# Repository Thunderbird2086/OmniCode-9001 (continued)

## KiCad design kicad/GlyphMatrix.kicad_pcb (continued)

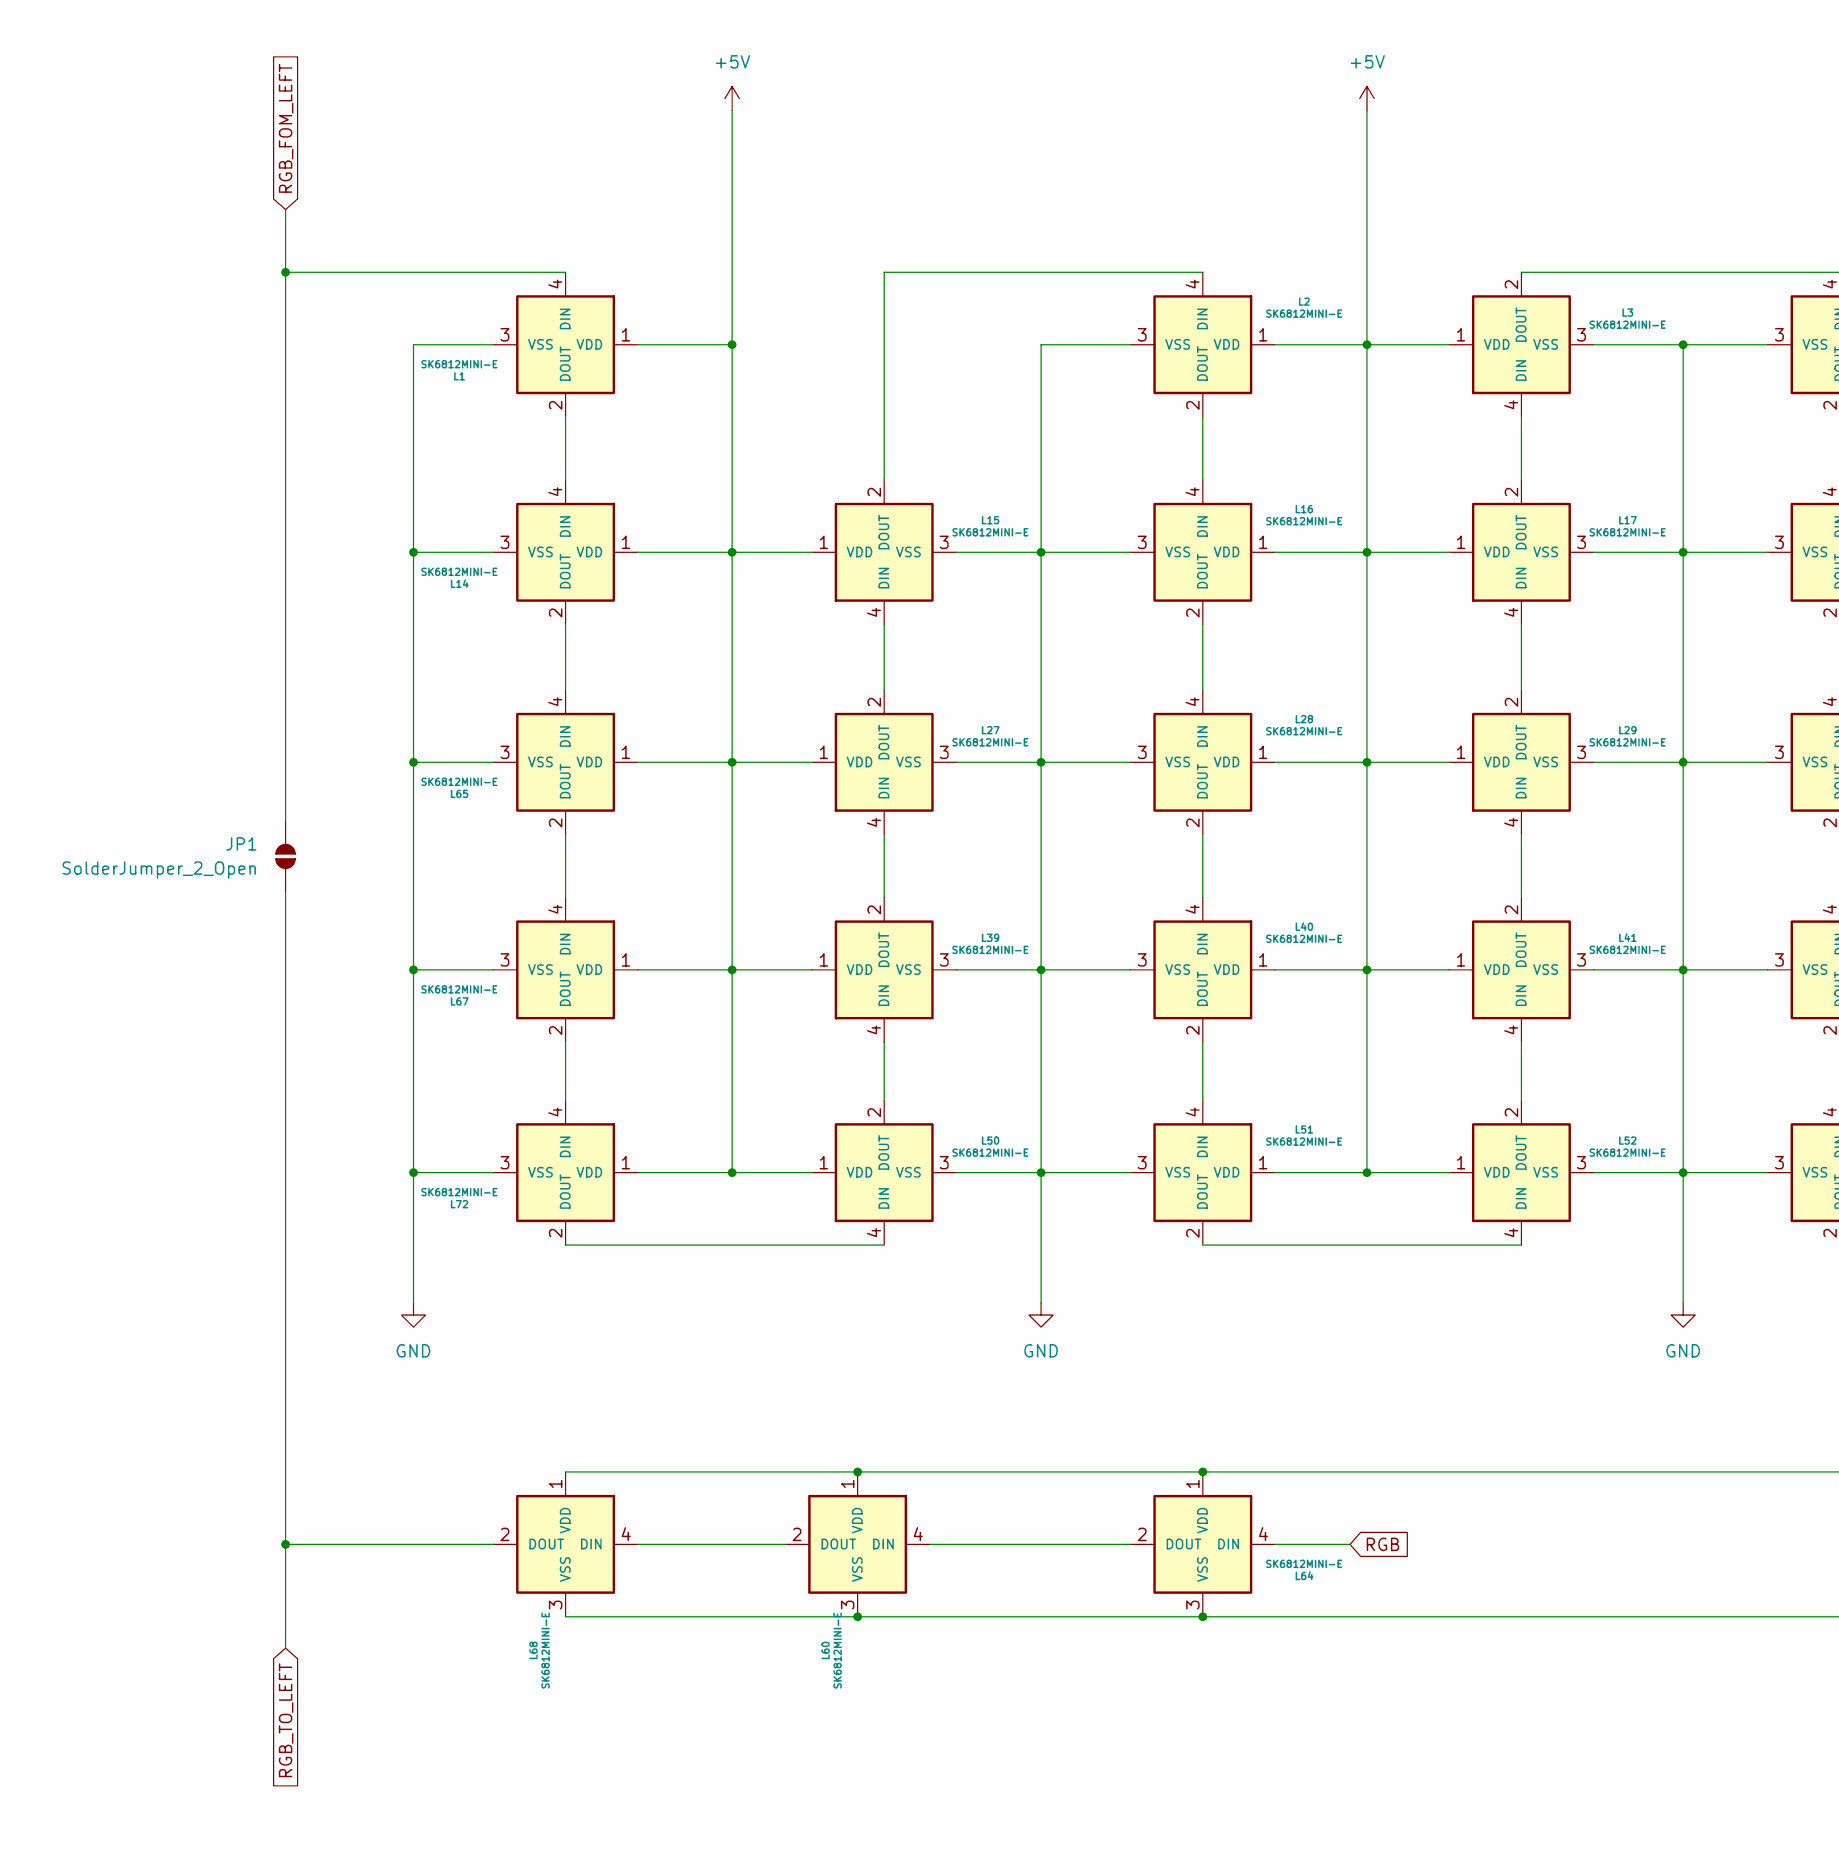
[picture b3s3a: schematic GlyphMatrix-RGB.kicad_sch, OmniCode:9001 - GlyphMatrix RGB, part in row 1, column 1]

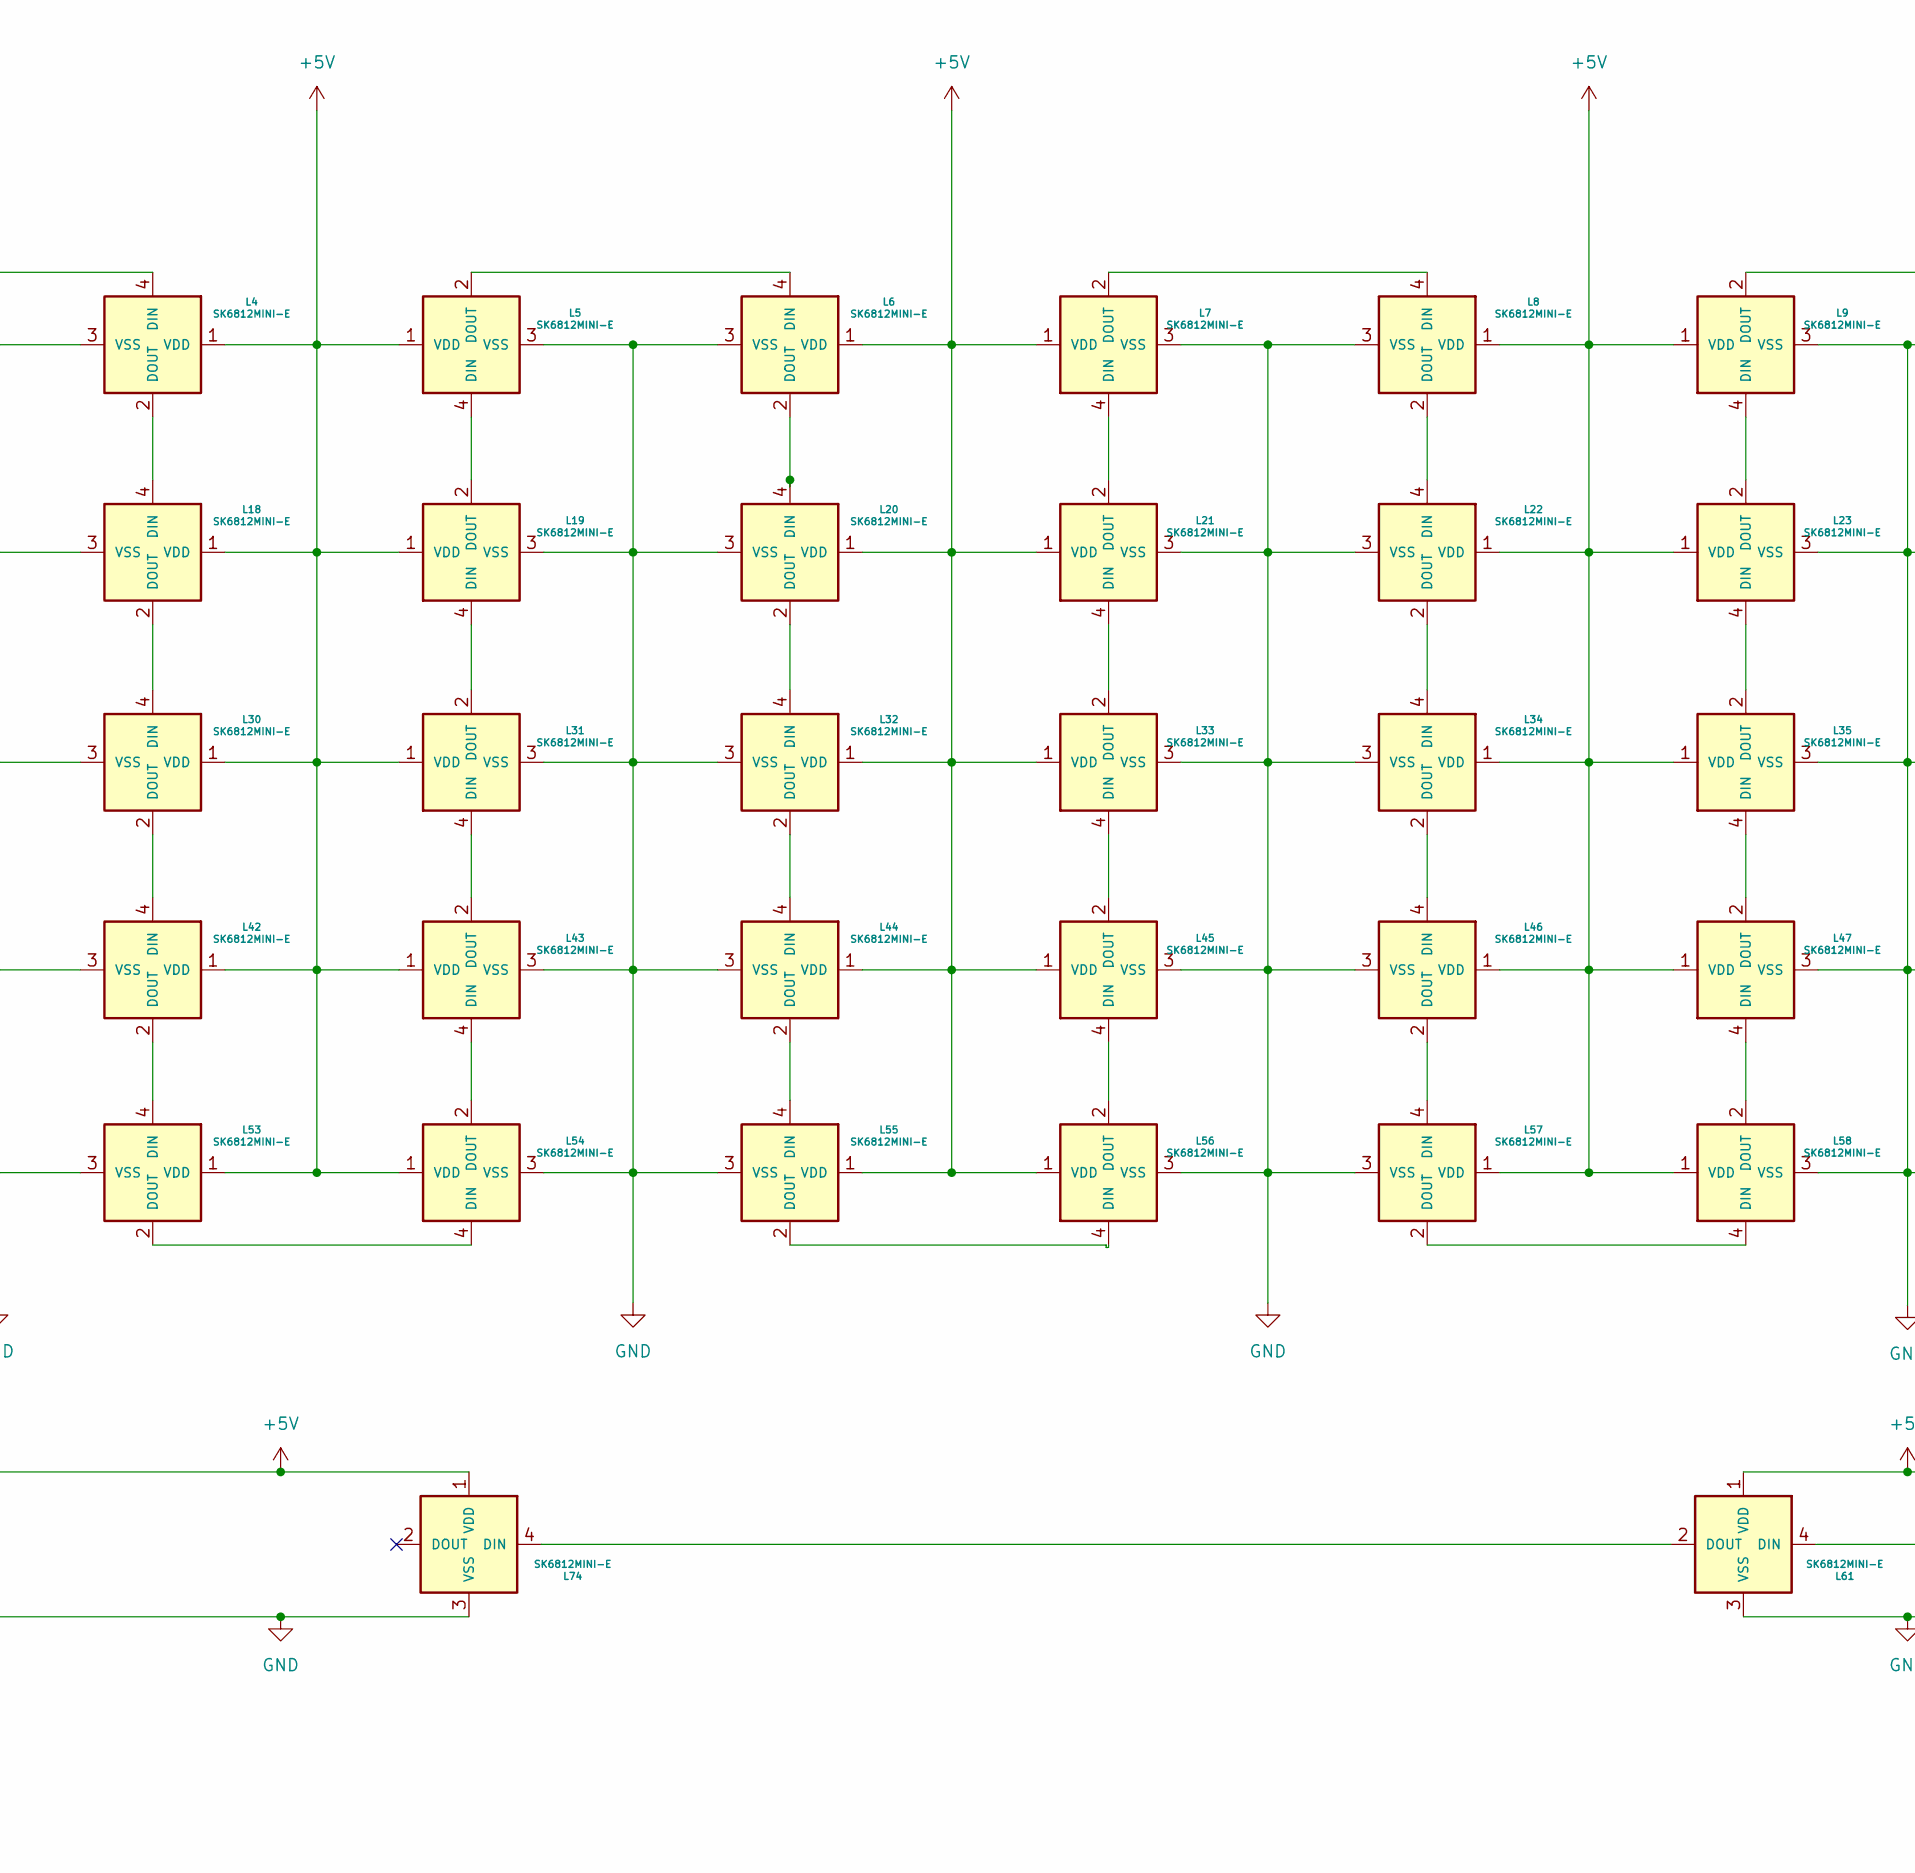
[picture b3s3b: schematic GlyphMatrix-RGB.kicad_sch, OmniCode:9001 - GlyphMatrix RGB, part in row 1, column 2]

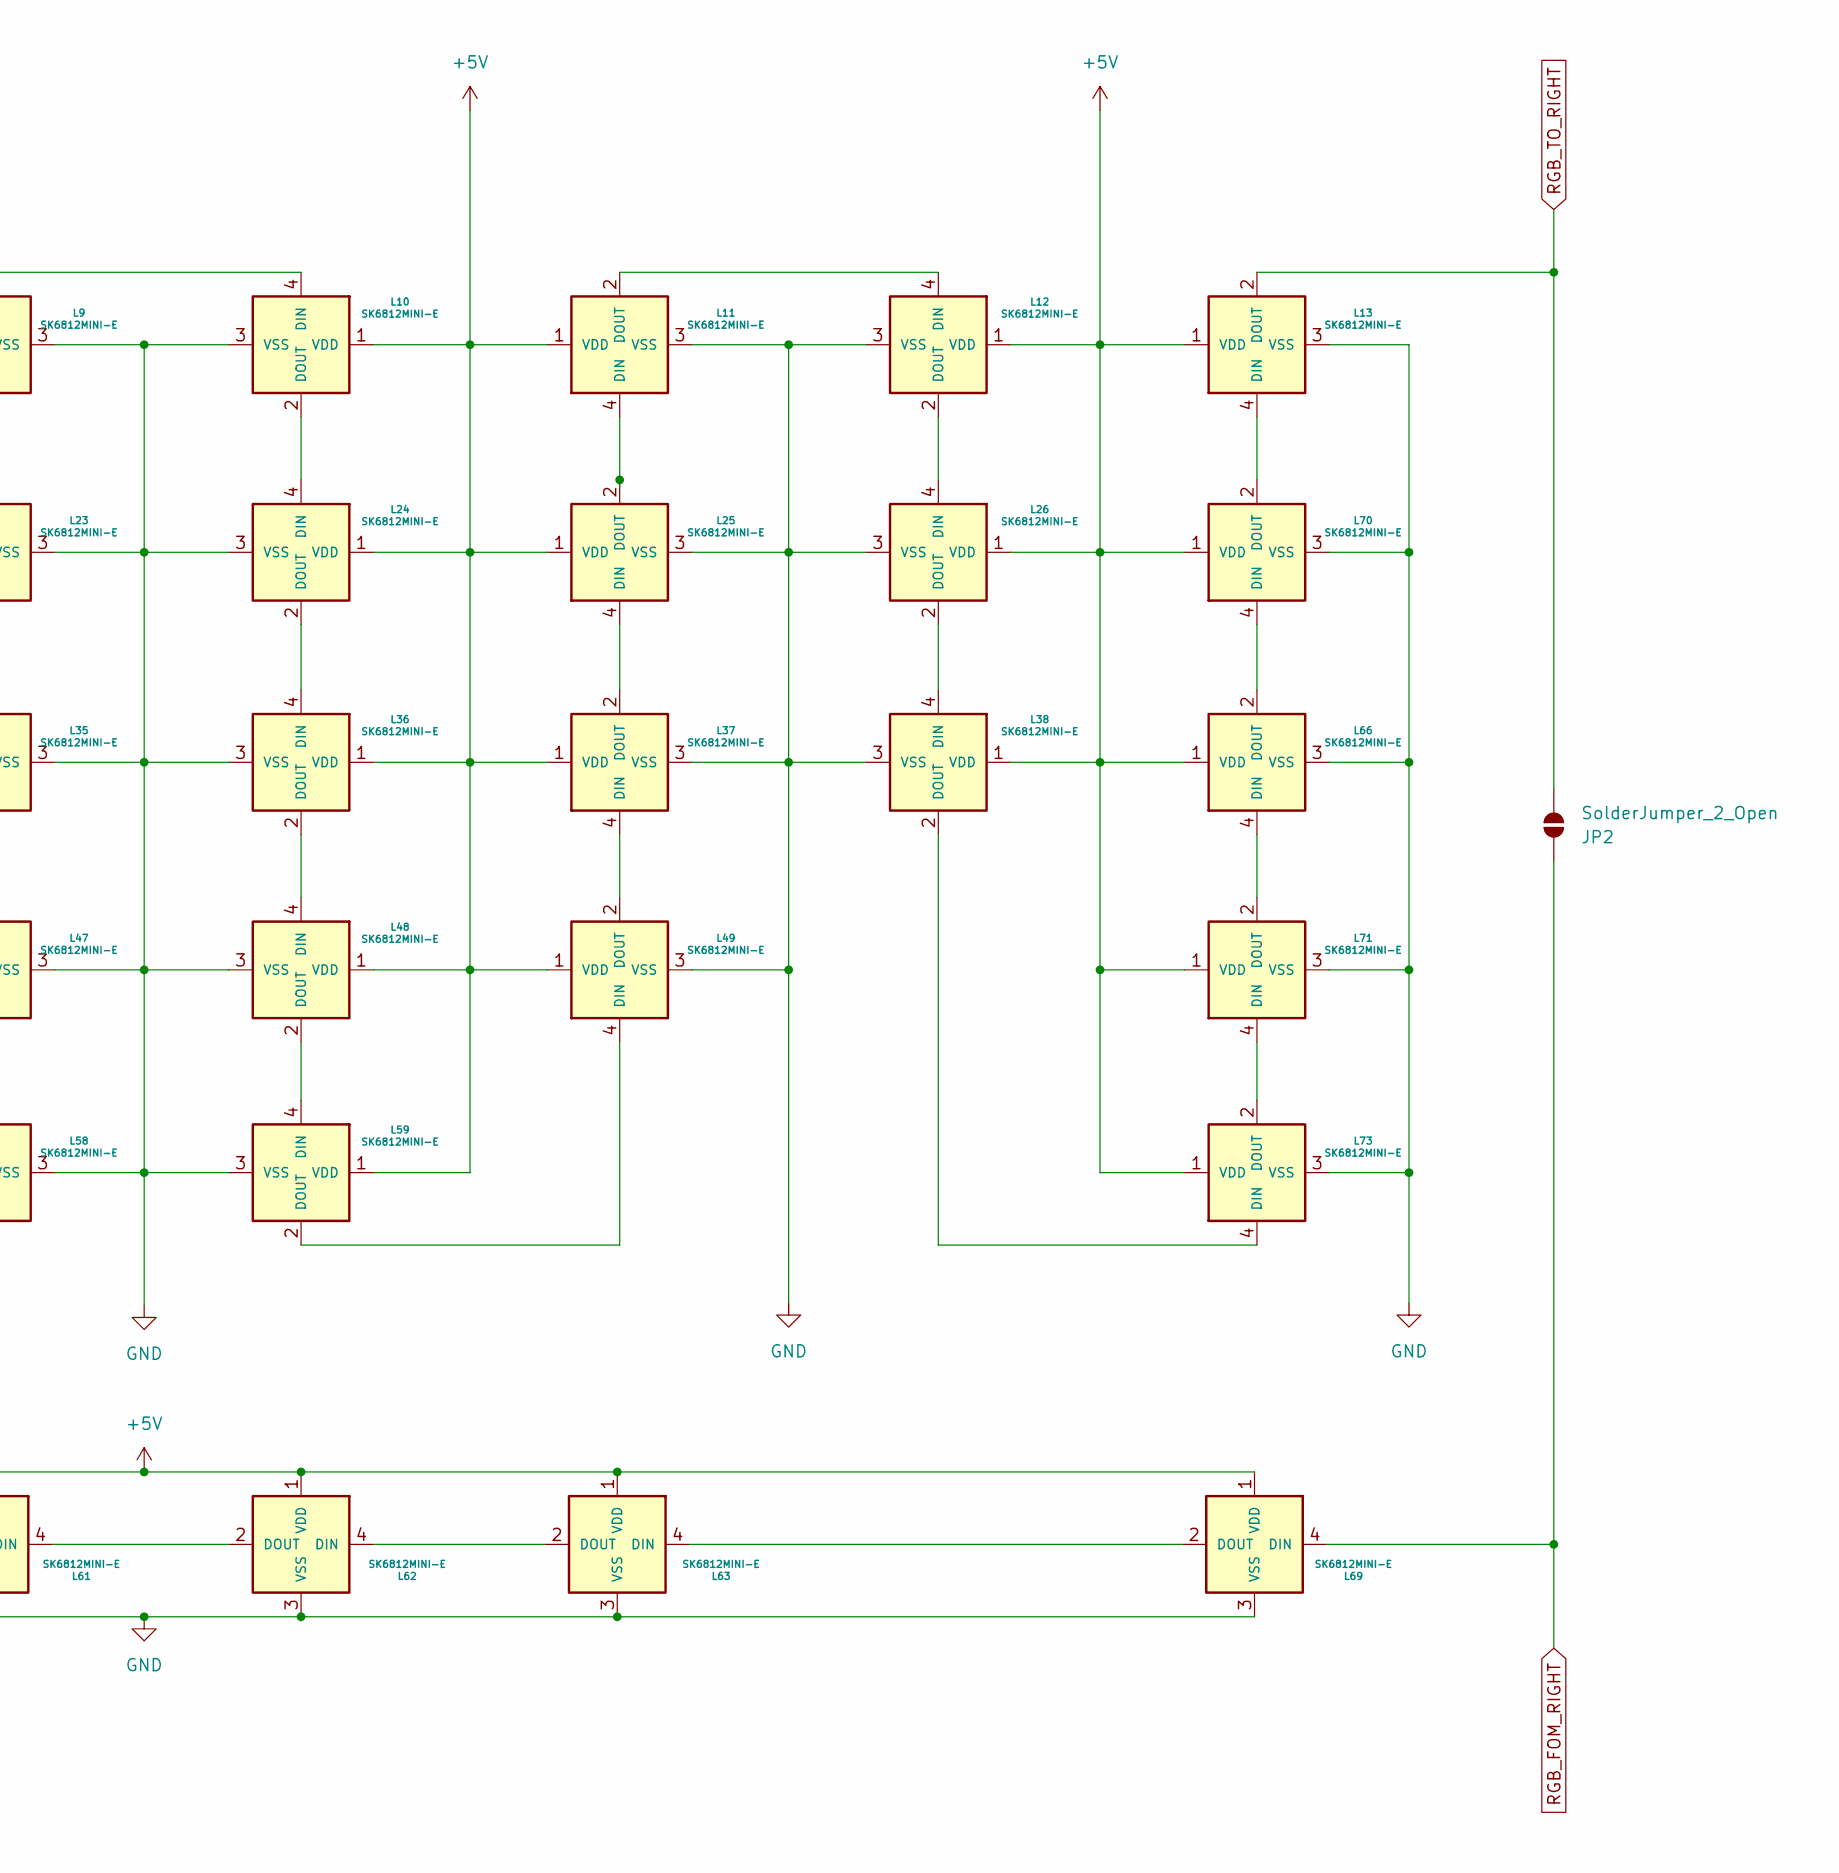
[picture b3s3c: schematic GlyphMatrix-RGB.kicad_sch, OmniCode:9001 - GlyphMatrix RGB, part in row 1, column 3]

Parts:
JP1, JP2: SolderJumper_2_Open; SolderJumper-2_P1.3mm_Bridged_RoundedPad1.0x1.5mm
L1, L2, L3, L4, L5, L6, L7, L8, L9, L10, L11, L12, L13, L14, L15, L16, L17, L18, L19, L20, L21, L22, L23, L24, L25, L26, L27, L28, L29, L30, L31, L32, L33, L34, L35, L36, L37, L38, L39, L40, L41, L42, L43, L44, L45, L46, L47, L48, L49, L50, L51, L52, L53, L54, L55, L56, L57, L58, L59, L60, L61, L62, L63, L64, L65, L66, L67, L68, L69, L70, L71, L72, L73, L74: SK6812MINI-E; LED_SK6812MINI-E; LCSC C5149201

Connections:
+5V: L1.1 (VDD), L2.1 (VDD), L3.1 (VDD), L4.1 (VDD), L5.1 (VDD), L6.1 (VDD), L7.1 (VDD), L8.1 (VDD), L9.1 (VDD), L10.1 (VDD), L11.1 (VDD), L12.1 (VDD), L13.1 (VDD), L14.1 (VDD), L15.1 (VDD), L16.1 (VDD), L17.1 (VDD), L18.1 (VDD), L19.1 (VDD), L20.1 (VDD), L21.1 (VDD), L22.1 (VDD), L23.1 (VDD), L24.1 (VDD), L25.1 (VDD), L26.1 (VDD), L27.1 (VDD), L28.1 (VDD), L29.1 (VDD), L30.1 (VDD), L31.1 (VDD), L32.1 (VDD), L33.1 (VDD), L34.1 (VDD), L35.1 (VDD), L36.1 (VDD), L37.1 (VDD), L38.1 (VDD), L39.1 (VDD), L40.1 (VDD), L41.1 (VDD), L42.1 (VDD), L43.1 (VDD), L44.1 (VDD), L45.1 (VDD), L46.1 (VDD), L47.1 (VDD), L48.1 (VDD), L49.1 (VDD), L50.1 (VDD), L51.1 (VDD), L52.1 (VDD), L53.1 (VDD), L54.1 (VDD), L55.1 (VDD), L56.1 (VDD), L57.1 (VDD), L58.1 (VDD), L59.1 (VDD), L60.1 (VDD), L61.1 (VDD), L62.1 (VDD), L63.1 (VDD), L64.1 (VDD), L65.1 (VDD), L66.1 (VDD), L67.1 (VDD), L68.1 (VDD), L69.1 (VDD), L70.1 (VDD), L71.1 (VDD), L72.1 (VDD), L73.1 (VDD), L74.1 (VDD); also elsewhere on the board
GND: L1.3 (VSS), L2.3 (VSS), L3.3 (VSS), L4.3 (VSS), L5.3 (VSS), L6.3 (VSS), L7.3 (VSS), L8.3 (VSS), L9.3 (VSS), L10.3 (VSS), L11.3 (VSS), L12.3 (VSS), L13.3 (VSS), L14.3 (VSS), L15.3 (VSS), L16.3 (VSS), L17.3 (VSS), L18.3 (VSS), L19.3 (VSS), L20.3 (VSS), L21.3 (VSS), L22.3 (VSS), L23.3 (VSS), L24.3 (VSS), L25.3 (VSS), L26.3 (VSS), L27.3 (VSS), L28.3 (VSS), L29.3 (VSS), L30.3 (VSS), L31.3 (VSS), L32.3 (VSS), L33.3 (VSS), L34.3 (VSS), L35.3 (VSS), L36.3 (VSS), L37.3 (VSS), L38.3 (VSS), L39.3 (VSS), L40.3 (VSS), L41.3 (VSS), L42.3 (VSS), L43.3 (VSS), L44.3 (VSS), L45.3 (VSS), L46.3 (VSS), L47.3 (VSS), L48.3 (VSS), L49.3 (VSS), L50.3 (VSS), L51.3 (VSS), L52.3 (VSS), L53.3 (VSS), L54.3 (VSS), L55.3 (VSS), L56.3 (VSS), L57.3 (VSS), L58.3 (VSS), L59.3 (VSS), L60.3 (VSS), L61.3 (VSS), L62.3 (VSS), L63.3 (VSS), L64.3 (VSS), L65.3 (VSS), L66.3 (VSS), L67.3 (VSS), L68.3 (VSS), L69.3 (VSS), L70.3 (VSS), L71.3 (VSS), L72.3 (VSS), L73.3 (VSS), L74.3 (VSS); also elsewhere on the board
unnamed: L1.2 (DOUT), L14.4 (DIN)
unnamed: L3.2 (DOUT), L4.4 (DIN)
unnamed: L5.2 (DOUT), L6.4 (DIN)
unnamed: L7.2 (DOUT), L8.4 (DIN)
unnamed: L9.2 (DOUT), L10.4 (DIN)
unnamed: L10.2 (DOUT), L24.4 (DIN)
unnamed: L11.4 (DIN), L25.2 (DOUT)
unnamed: L11.2 (DOUT), L12.4 (DIN)
unnamed: L12.2 (DOUT), L26.4 (DIN)
unnamed: L13.4 (DIN), L70.2 (DOUT)
unnamed: L14.2 (DOUT), L65.4 (DIN)
unnamed: L15.4 (DIN), L27.2 (DOUT)
unnamed: L2.4 (DIN), L15.2 (DOUT)
unnamed: L2.2 (DOUT), L16.4 (DIN)
unnamed: L16.2 (DOUT), L28.4 (DIN)
unnamed: L17.4 (DIN), L29.2 (DOUT)
unnamed: L3.4 (DIN), L17.2 (DOUT)
unnamed: L4.2 (DOUT), L18.4 (DIN)
unnamed: L18.2 (DOUT), L30.4 (DIN)
unnamed: L19.4 (DIN), L31.2 (DOUT)
unnamed: L5.4 (DIN), L19.2 (DOUT)
unnamed: L6.2 (DOUT), L20.4 (DIN)
unnamed: L20.2 (DOUT), L32.4 (DIN)
unnamed: L21.4 (DIN), L33.2 (DOUT)
unnamed: L7.4 (DIN), L21.2 (DOUT)
unnamed: L8.2 (DOUT), L22.4 (DIN)
unnamed: L22.2 (DOUT), L34.4 (DIN)
unnamed: L23.4 (DIN), L35.2 (DOUT)
unnamed: L9.4 (DIN), L23.2 (DOUT)
unnamed: L24.2 (DOUT), L36.4 (DIN)
unnamed: L25.4 (DIN), L37.2 (DOUT)
unnamed: L26.2 (DOUT), L38.4 (DIN)
unnamed: L27.4 (DIN), L39.2 (DOUT)
unnamed: L28.2 (DOUT), L40.4 (DIN)
unnamed: L29.4 (DIN), L41.2 (DOUT)
unnamed: L30.2 (DOUT), L42.4 (DIN)
unnamed: L31.4 (DIN), L43.2 (DOUT)
unnamed: L32.2 (DOUT), L44.4 (DIN)
unnamed: L33.4 (DIN), L45.2 (DOUT)
unnamed: L34.2 (DOUT), L46.4 (DIN)
unnamed: L35.4 (DIN), L47.2 (DOUT)
unnamed: L36.2 (DOUT), L48.4 (DIN)
unnamed: L37.4 (DIN), L49.2 (DOUT)
unnamed: L38.2 (DOUT), L73.4 (DIN)
unnamed: L39.4 (DIN), L50.2 (DOUT)
unnamed: L40.2 (DOUT), L51.4 (DIN)
unnamed: L41.4 (DIN), L52.2 (DOUT)
unnamed: L42.2 (DOUT), L53.4 (DIN)
unnamed: L43.4 (DIN), L54.2 (DOUT)
unnamed: L44.2 (DOUT), L55.4 (DIN)
unnamed: L45.4 (DIN), L56.2 (DOUT)
unnamed: L46.2 (DOUT), L57.4 (DIN)
unnamed: L47.4 (DIN), L58.2 (DOUT)
unnamed: L48.2 (DOUT), L59.4 (DIN)
unnamed: L49.4 (DIN), L59.2 (DOUT)
unnamed: L50.4 (DIN), L72.2 (DOUT)
unnamed: L51.2 (DOUT), L52.4 (DIN)
unnamed: L53.2 (DOUT), L54.4 (DIN)
unnamed: L55.2 (DOUT), L56.4 (DIN)
unnamed: L57.2 (DOUT), L58.4 (DIN)
unnamed: L60.4 (DIN), L64.2 (DOUT)
unnamed: L60.2 (DOUT), L68.4 (DIN)
unnamed: L61.4 (DIN), L62.2 (DOUT)
unnamed: L61.2 (DOUT), L74.4 (DIN)
unnamed: L62.4 (DIN), L63.2 (DOUT)
unnamed: L63.4 (DIN), L69.2 (DOUT)
unnamed: L65.2 (DOUT), L67.4 (DIN)
unnamed: L66.4 (DIN), L71.2 (DOUT)
unnamed: L66.2 (DOUT), L70.4 (DIN)
unnamed: L67.2 (DOUT), L72.4 (DIN)
unnamed: L71.4 (DIN), L73.2 (DOUT)
RGB: L64.4 (DIN); also elsewhere on the board
RGB_FOM_LEFT: JP1.2 (B), L1.4 (DIN); also elsewhere on the board
RGB_FOM_RIGHT: JP2.2 (B), L69.4 (DIN); also elsewhere on the board
RGB_TO_LEFT: JP1.1 (A), L68.2 (DOUT); also elsewhere on the board
RGB_TO_RIGHT: JP2.1 (A), L13.2 (DOUT); also elsewhere on the board

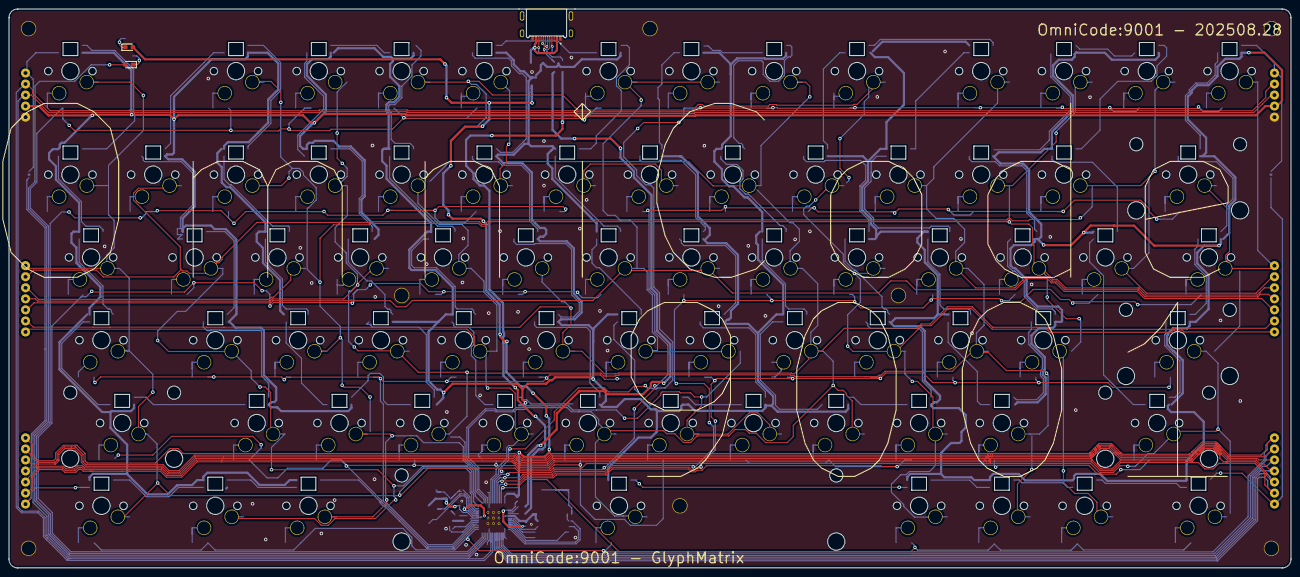
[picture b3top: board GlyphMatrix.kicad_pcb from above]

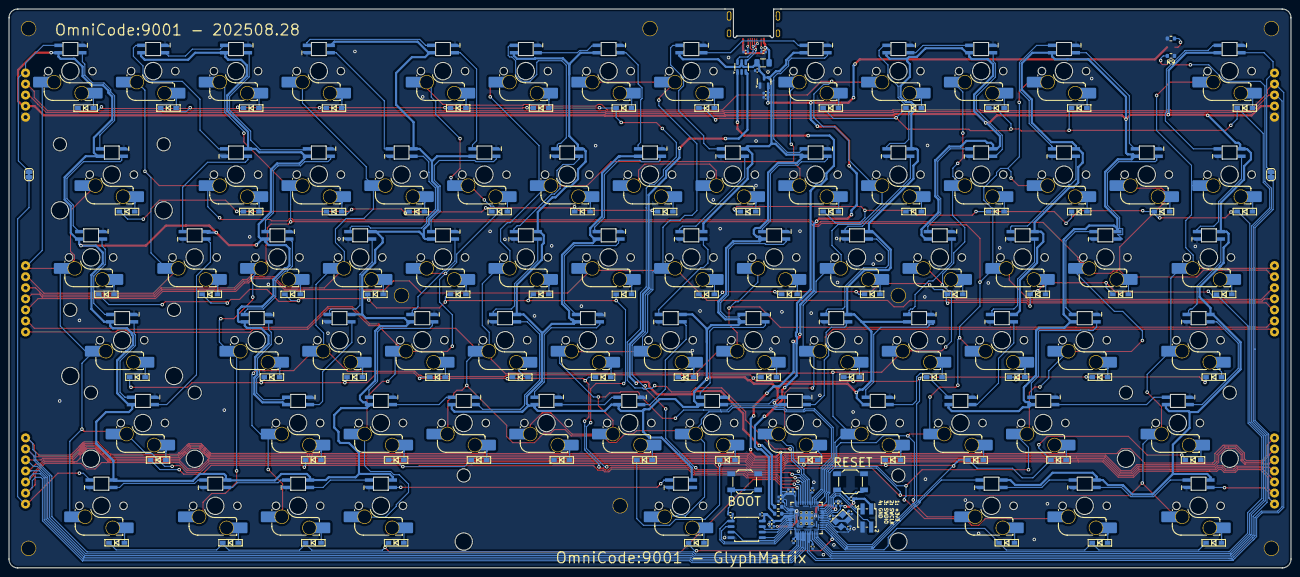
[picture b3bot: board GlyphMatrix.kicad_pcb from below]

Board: 2 copper layers, 294.9 x 128.6 mm, 281 parts (265 on the bottom side), 206 nets.

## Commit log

2025-07-09 added submodule
2025-07-09 split up boards
2025-07-09 added ergogen yaml
2025-07-09 added kicad
2025-07-09 artwork
2025-07-09 artwork for PhaseShift
2025-07-09 pogo pin - ergogen
2025-07-09 updated MCU
2025-07-09 artwork for GlyphMatrix
2025-07-09 pogo pin connectors
2025-07-09 artwork #2
2025-07-09 changed screw sizes
2025-07-09 artwork #3
2025-07-09 Silk Screen
2025-07-09 screw holes
2025-07-09 added MCU
2025-07-09 artwork for DeltaForm
2025-07-09 RGB schematic
2025-07-09 3D Models
2025-07-09 fixed positions for screw holes
2025-07-09 initial commit (#1)
    * added submodule
    * added ergogen yaml
    * split up boards
    * added kicad
    * added MCU
    * updated MCU
2025-07-10 added BOM
2025-07-10 added BOM files
2025-07-10 BOM (#2)
    * updated README.md
    * added BOM
    * reorg BOM files
2025-07-10 small tweaks
2025-07-11 GlyphMatrix - 3mm screws
2025-07-11 PhaseShift - 3mm screws
2025-07-11 DeltaForm - 3mm screws
2025-07-11 more tweaks (#3)
    * small tweaks
    * GlyphMatrix - 3mm screws
    * PhaseShift - 3mm screws
    * DeltaForm - 3mm screws
    * updated README.md
2025-07-12 small changes for GlyphMatrix
2025-07-13 Silk screen for plates
2025-07-13 amended GlyphMatrix
2025-07-13 plates (#4)
    * Silk Screen
    * small changes for GlyphMatrix
    * Silk screen for plates
    * amended GlyphMatrix
2025-07-13 build guilde - WIP
2025-07-13 updatped README.md
2025-07-13 doc (#5)
    * Silk Screen
    * updatped README.md
    * build guilde - WIP
2025-07-15 updated ergogen
2025-07-15 updated build guide for GlyphMatrix
2025-07-15 build guide - GlyphMatrix (#6)
    * updated ergogen
    * updated build guide for GlyphMatrix
2025-07-15 updated build guide - GlyphMatrix
2025-07-15 updated build guide - GlyphMatrix (#7)
2025-07-16 updated build guide - GlyphMatrix
    * pogo pin
2025-07-16 updated images
2025-07-16 updated build guide - GlyphMatrix
    * bottom plate
2025-07-16 update build guide for GlyphMatrix (#8)
    * updated build guide - GlyphMatrix
    * pogo pin
    * updated images
    * updated build guide - GlyphMatrix
    * bottom plate
2025-07-16 added build guides for PhaseShift and DeltaForm
2025-07-16 build guides (#9)
    * added build guides for PhaseShift and DeltaForm
    * updated README.md
2025-07-16 fixed layout json
2025-07-16 updated ergogen - stabilizers
2025-07-17 updated BOM
2025-07-17 2U stabilizers for ergogen (#10)
    * fixed layout json
    * updated ergogen - stabilizers
    * updated BOM
2025-07-19 kibot
2025-07-19 kibot (#11)
2025-07-19 working on kibot
2025-07-19 added position file
2025-07-20 fixed footprint for PhaseShift and DeltaForm
2025-07-20 fixed footprint side for GlyphMatrix
2025-07-20 KiBot: changed BOM type
2025-07-20 added fonts
2025-07-21 refreshed submodule
2025-07-21 updated footprint for GlyphMatrix
2025-07-21 updated footprint for PhaseShift
2025-07-21 updated footprint for DeltaForm
2025-07-21 updated build guide
2025-07-21 more updates (#12)
    * working on kibot
    * added position file
    * fixed footprint for PhaseShift and DeltaForm
    * fixed footprint side for GlyphMatrix
    * KiBot: changed BOM type
    * added fonts
2025-07-21 Changed fonts for silk screen
2025-07-21 updated fonts for PhaseShift
2025-07-21 updated fonts for DeltaForm
2025-07-21 updated kibot for GlyphMatrix
2025-07-22 added dummy schematic files for GlyphMatrix
2025-07-22 updated kibot config
2025-07-22 added PhaseShift to workflow
2025-07-22 added DeltaForm to workflow
2025-07-22 updated fonts (#13)
    * Changed fonts for silk screen
    * updated fonts for PhaseShift
    * updated fonts for DeltaForm
    * updated kibot for GlyphMatrix
    * added dummy schematic files for GlyphMatrix
    * updated kibot config
2025-07-22 updated build guide (#14)
2025-07-22 small tweak
2025-07-22 small tweak (#15)
2025-07-22 added a missing image
2025-07-22 added a missing image (#16)
2025-07-23 fixed BOM
2025-07-23 adedd colemak-dh
2025-07-23 correct gui/opt positions
2025-07-23 fixed BOM (#17)
    * fixed BOM
    * adedd colemak-dh
    * correct gui/opt positions
2025-07-28 reorg schematic for GlyphMatrix
2025-07-28 reorg schematic for PhaseShift
2025-07-28 reorg schematic for DeltaForm
2025-07-28 reorg schematic (#18)
    * GlyphMatrix
    * PhaseShift
    * DeltaForm
2025-07-30 reorg directory structure
2025-07-30 added key cap size to build guide
2025-07-30 updated build guide (#19)
    * reorg directory structure
    * updated build guide
    * added key cap size to build guide
2025-08-03 updated schematic for GlyphMatrix
2025-08-03 updated schematic for GlyphMatrix (#20)
2025-08-04 adjusted positions
    - pogo pins
2025-08-04 small tweak
    - pogo pin
2025-08-04 202508.04
2025-08-04 adjust pogo pin positions (#21)
    * adjusted positions
    * small tweak
    * updated ergogen
    * 202508.04
2025-08-09 removed isolated copper islands
2025-08-09 tweaked zone (#22)
    * small tweak
    * removed isolated copper islands
2025-08-09 202508.10
2025-08-09 202508.10 (#23)
2025-08-10 fixed images
2025-08-15 fixed images (#24)
2025-08-17 side bars
2025-08-17 side bars (#25)
2025-08-28 fixed LED for GlyphMatrix
2025-08-28 fixed LED for GlyphMatrix (#26)
2025-08-29 fixed mounting hole for GlyphMatrix
2025-08-29 fixed mounting hole for GlyphMatrix (#27)
2025-08-31 fixed build guide for GlyphMatrix
2025-08-31 fixed build guide for GlyphMatrix (#28)
2025-09-06 updated required parts for GlyphMatrix
2025-09-06 Update build guide (#29)
    * updated build guide
    * updated required parts for GlyphMatrix
    * small tweaks
2025-09-16 quick fix
2025-09-16 quick fix (#30)
2025-09-21 updated 3D models
2025-09-21 cases
2025-09-21 updated top level README.md
2025-09-21 cases (#31)
    * updated 3D models
    * cases
    * updated top level README.md
2025-09-21 added the case image
2025-09-21 README.md
